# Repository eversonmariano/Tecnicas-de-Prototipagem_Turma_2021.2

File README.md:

######################
TÉCNICAS DE PROTOTIPAGEM  ** INDIVIDUAL **
######################

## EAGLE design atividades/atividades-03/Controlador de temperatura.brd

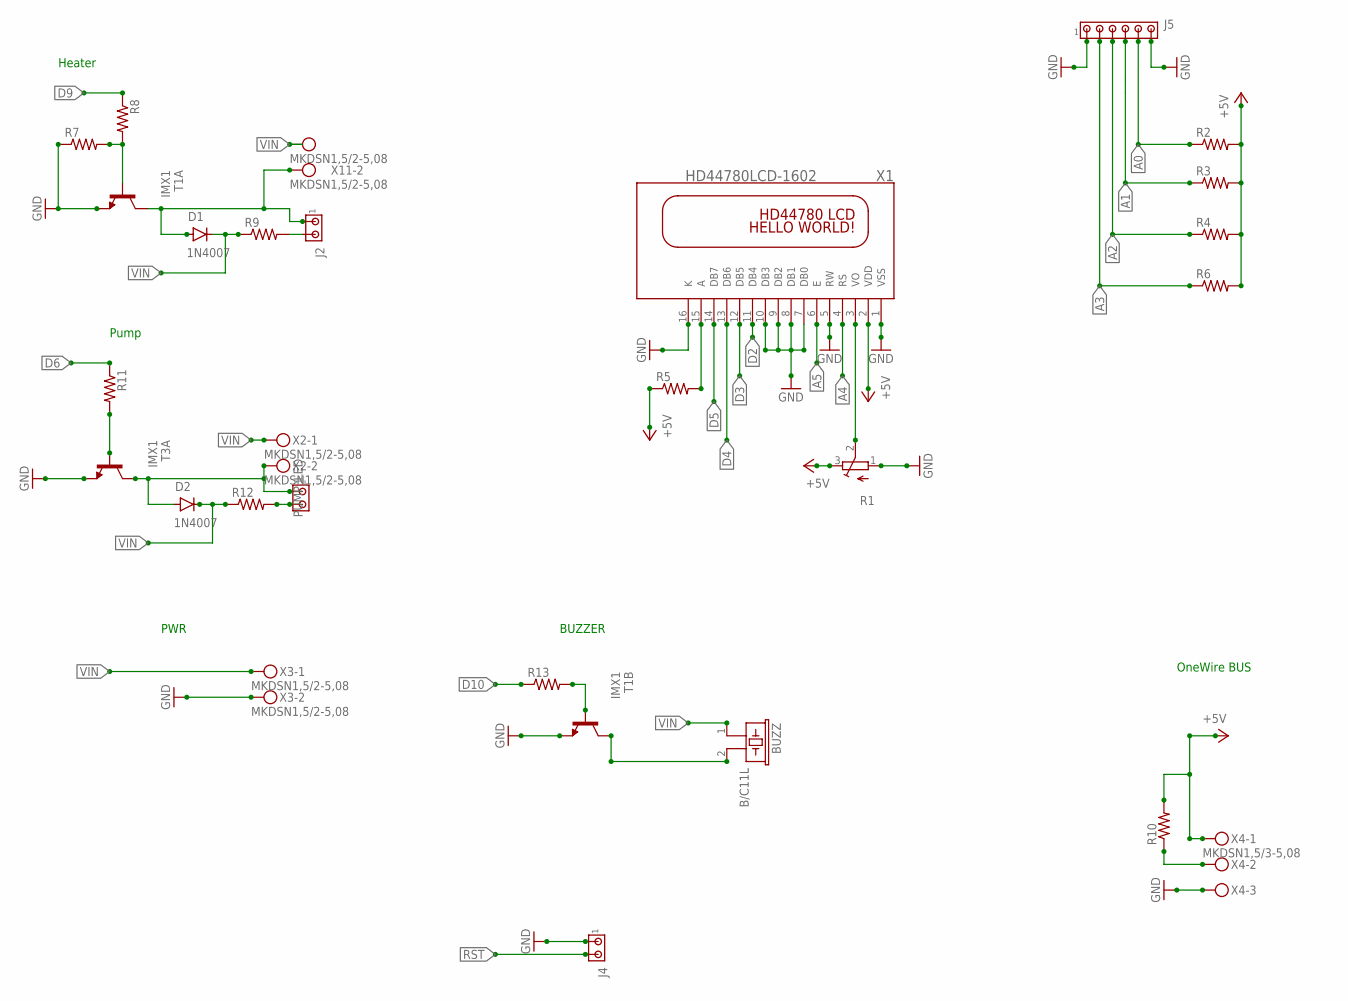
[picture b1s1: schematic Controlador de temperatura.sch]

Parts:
BUZZ: B/C11L
D1, D2: 1N4007; DO-41
J2, J4: MTA02-156; 1X2MTA
J5: MTA06-100; 10X06MTA
PUMP_LED: MTA02-156; 1X2MTA
R1: TRIM_EU-3223W; 3223W
R2, R3, R4, R5, R6, R7, R8, R9, R10, R11, R12, R13: R-US_0204/7; 0204/7
T1, T3: IMX1; SMT6
X1: HD44780LCD-1602; LCD1602
X2, X3, X11: MKDSN1,5/2-5,08
X4: MKDSN1,5/3-5,08

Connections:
+5V: R1.3 (E), R2.2, R3.2, R4.2, R5.1, R6.2, R10.2, X1.2 (VDD), X4.1
A0: J5.5, R2.1
A1: J5.4, R3.1
A2: J5.3, R4.1
A3: J5.2, R6.1
A4: X1.4 (RS)
A5: X1.6 (E)
D2: X1.11 (DB4)
D3: X1.12 (DB5)
D4: X1.13 (DB6)
D5: X1.14 (DB7)
D6: R11.1
D9: R8.1
D10: R13.1
GND: J4.1, J5.1, J5.6, R1.1 (A), R7.1, T1.3 (E), T1.6 (E), T3.6 (E), X1.1 (VSS), X1.5 (RW), X1.7 (DB0), X1.8 (DB1), X1.9 (DB2), X1.10 (DB3), X1.16 (K), X3.2, X4.3
unnamed: R5.2, X1.15 (A)
unnamed: BUZZ.2, T1.4 (C)
unnamed: R1.2 (S), X1.3 (VO)
unnamed: D1.A, J2.1, T1.1 (C), X11.2
unnamed: R7.2, R8.2, T1.5 (B)
unnamed: D2.A, PUMP_LED.1, T3.1 (C), X2.2
unnamed: R11.2, T3.5 (B)
unnamed: J2.2, R9.2
unnamed: PUMP_LED.2, R12.2
unnamed: R10.1, X4.2
unnamed: R13.2, T1.2 (B)
RST: J4.2
VIN: BUZZ.1, D1.C, D2.C, R9.1, R12.1, X2.1, X3.1, X11.1

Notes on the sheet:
Heater
Pump
PWR
BUZZER
OneWire BUS

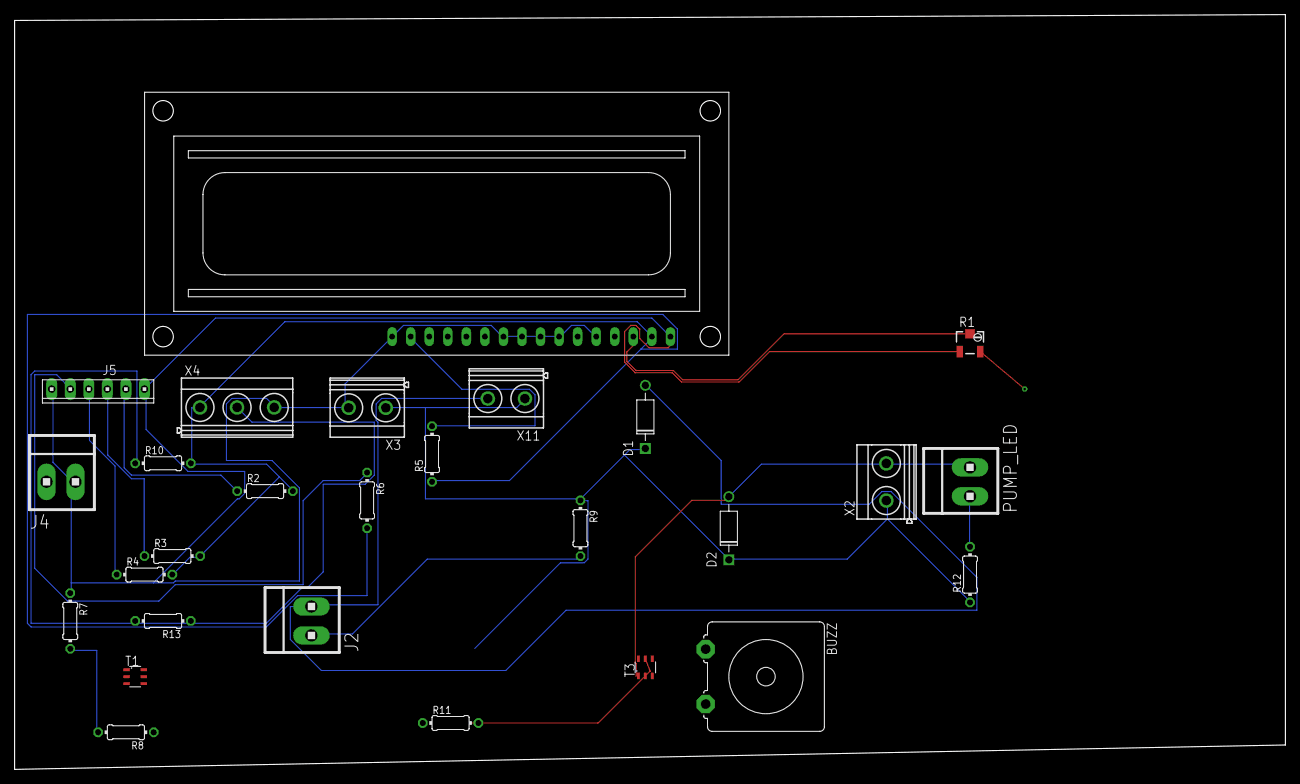
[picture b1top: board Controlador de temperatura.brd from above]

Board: 2 copper layers, 174.0 x 103.3 mm, 27 parts (0 on the bottom side), 18 nets.

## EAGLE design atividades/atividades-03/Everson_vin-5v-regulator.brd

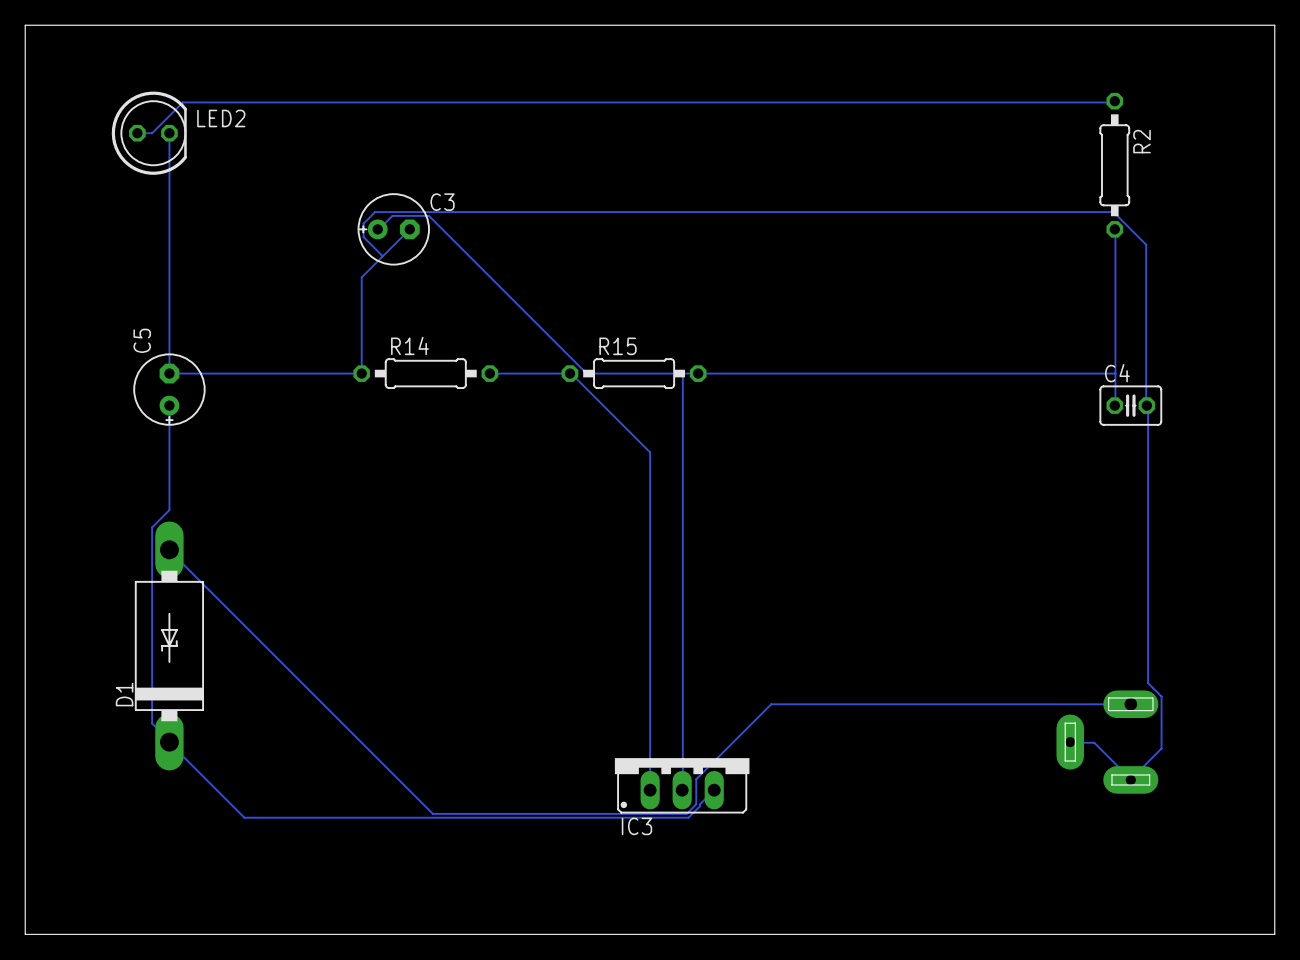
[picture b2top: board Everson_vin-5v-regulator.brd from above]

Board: 2 copper layers, 99.0 x 72.1 mm, 10 parts (1 on the bottom side), 6 nets.

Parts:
C3: 10uF; E2,5-6E
C4: 100nF; C025-030X050
C5: 47uF; E2,5-6E
D1: 1N5908; C4111-15
IC3: LM317; 317TS
J4: SPC4077
LED2: VERDE; LED5MM
R2: 1K; 0207/10
R14: 715; 0207/10
R15: 240; 0207/10

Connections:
+5V: C3.+, C4.1, IC3.2, R2.2, R15.2
GND: C3.-, C4.2, C5.-, J4.1, J4.2, LED2.K, R14.1
unnamed: D1.A, J4.3
unnamed: C5.+, D1.C, IC3.3
unnamed: IC3.1, R14.2, R15.1
unnamed: LED2.A, R2.1

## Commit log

2021-11-11 Primeiro commit
2021-12-04 Dummy_load_schematic
2021-12-14 atividade03_brd
2021-12-20 controladorTemperatura
2021-12-28 LCD_ERM2004-2
2022-01-12 modificando o README.md
